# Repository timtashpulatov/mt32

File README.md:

# mt32
Ghetto synth

Prosthetic parts for lonely MT-32 board once salvaged at local flea market

##### Table of Contents
[Switch board](#sw_board)

[LCD](#lcd)

[POWER_SW](#power_sw)

<a name="sw_board"/>

## Switch board

- Switch board and LCD
")
")
</a>

Original switches marked SKELAF in the Service Manual:

Looks very similar to modern SKPLAFD010 from ALPS [(Datasheet)](PDF/ALPS-SKPLAFD010.pdf)

SKELAK was used in the Roland MKS-20 https://telcontar.net/KBK/Alps/elastic_contact

Check out SKEGAEA010 (with stem) [(Datasheet)](PDF/ALPS-SKEGAEA010.pdf)

Possible switches replacement:

- Omron B3M-6009
- Panasonic EVQ-PV205K [(Datasheet)](PDF/Panasonic-EVQ-PVA05K.pdf)
- E-Switch TL1140AF070Q

EVQ-PVA05K:

<a name="lcd"/>

## LCD module
DM2011 from Sanyo, with Epson SED1200 controller
</a>

<a name="power_sw"/>

## Power Switch
SPUN19F from ALPS
https://tech.alpsalpine.com/prod/e/html/switch/push/spun/spun19c400.html

## NOTES
DM2011 LCD module is clocked from SO7 port (pin 74 of IC35), via RC filter R62 (1K) and C83 (22p)

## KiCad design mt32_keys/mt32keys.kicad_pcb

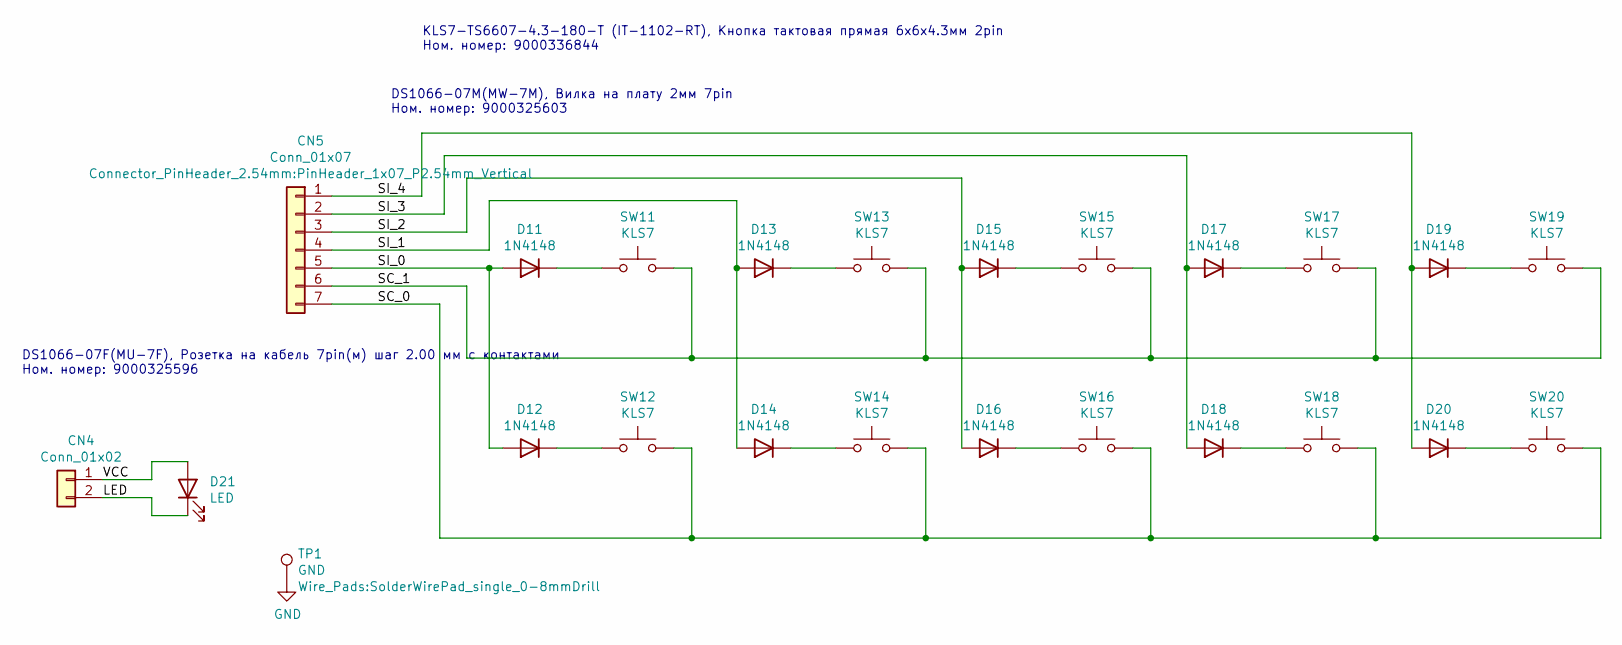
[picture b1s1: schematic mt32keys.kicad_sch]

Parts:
CN4: Conn_01x02; JST_NV_B02P-NV_2x5.00mm_Vertical
CN5: Conn_01x07; PinHeader_1x07_P2.54mm_Vertical
D11, D12, D13, D14, D15, D16, D17, D18, D19, D20: 1N4148; D_DO-35_SOD27_P10.16mm_Horizontal
D21: LED; LED_Rectangular_W3.0mm_H2.0mm
SW11, SW12, SW13, SW14, SW15, SW16, SW17, SW18, SW19, SW20: KLS7; KLS7-TS6607-4.3-180-T
TP1: GND; SolderWirePad_single_0-8mmDrill

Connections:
/LED: CN4.2, D21.1 (K)
/SC_0: CN5.7, SW12.2, SW14.2, SW16.2, SW18.2, SW20.2
/SC_1: CN5.6, SW11.2, SW13.2, SW15.2, SW17.2, SW19.2
/SI_0: CN5.5, D11.2 (A), D12.2 (A)
/SI_1: CN5.4, D13.2 (A), D14.2 (A)
/SI_2: CN5.3, D15.2 (A), D16.2 (A)
/SI_3: CN5.2, D17.2 (A), D18.2 (A)
/SI_4: CN5.1, D19.2 (A), D20.2 (A)
/VCC: CN4.1, D21.2 (A)
unnamed: D11.1 (K), SW11.1
unnamed: D12.1 (K), SW12.1
unnamed: D13.1 (K), SW13.1
unnamed: D14.1 (K), SW14.1
unnamed: D15.1 (K), SW15.1
unnamed: D16.1 (K), SW16.1
unnamed: D17.1 (K), SW17.1
unnamed: D18.1 (K), SW18.1
unnamed: D19.1 (K), SW19.1
unnamed: D20.1 (K), SW20.1

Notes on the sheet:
DS1066-07M(MW-7M), Вилка на плату 2мм 7pin Ном. номер: 9000325603
KLS7-TS6607-4.3-180-T (IT-1102-RT), Кнопка тактовая прямая 6х6х4.3мм 2pin Ном. номер: 9000336844
DS1066-07F(MU-7F), Розетка на кабель 7pin(м) шаг 2.00 мм с контактами Ном. номер: 9000325596

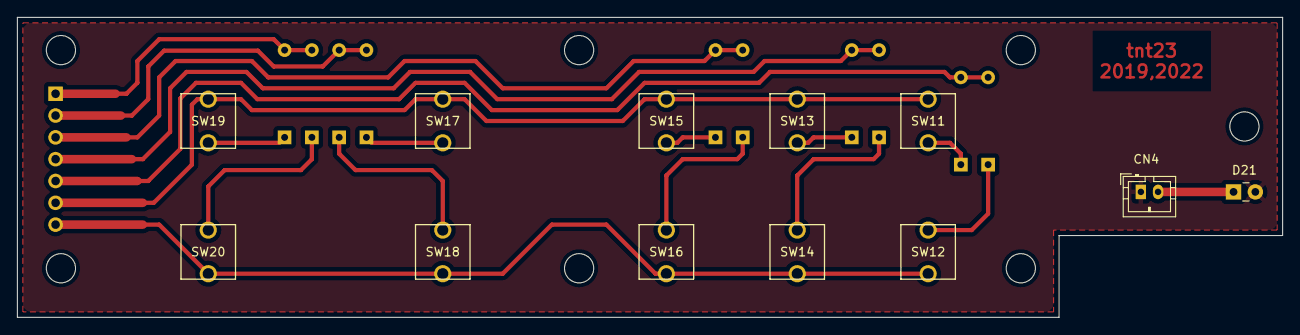
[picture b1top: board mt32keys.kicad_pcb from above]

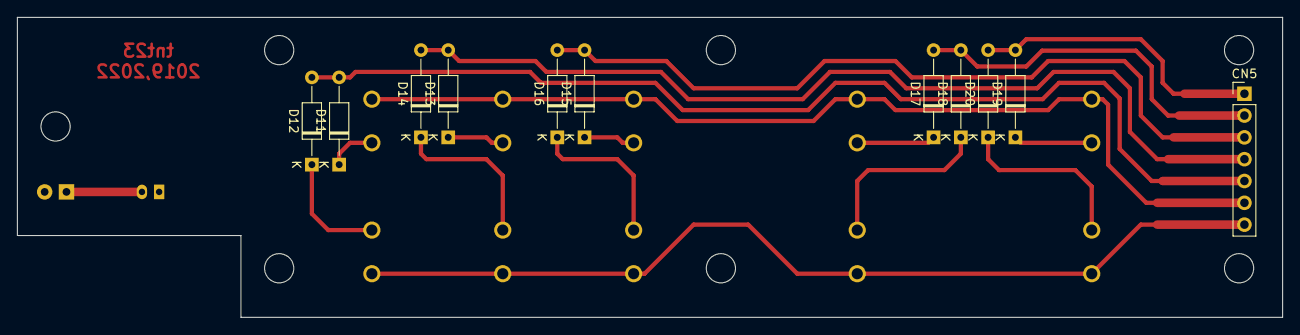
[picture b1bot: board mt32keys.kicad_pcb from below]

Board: 2 copper layers, 147.3 x 34.9 mm, 23 parts (11 on the bottom side), 19 nets.

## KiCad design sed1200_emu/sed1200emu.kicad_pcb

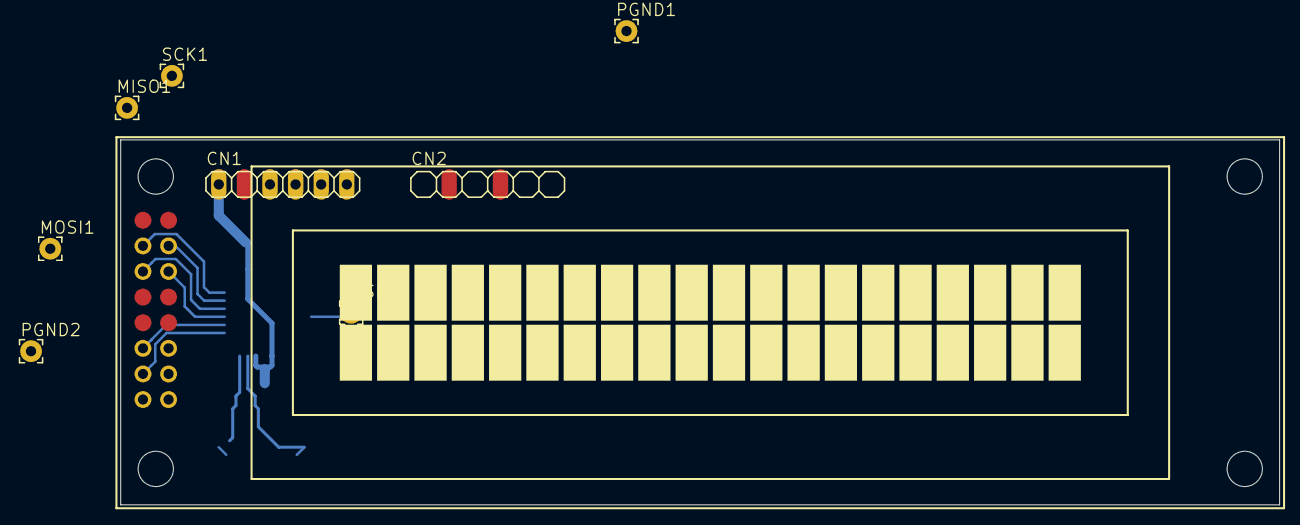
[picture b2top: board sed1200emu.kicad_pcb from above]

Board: 2 copper layers, 114.9 x 36.2 mm, 16 parts (0 on the bottom side), 21 nets.

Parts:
C1, C2: 0.1; C0805
C3, C4: 22p; C0805
CN1, CN2: PINHD-1X6; 1X06
DIS2: TUXGR_20X2
IC1: MEGA8-AI; TQFP32-08
MISO1: MISO; 2,15_1,0
MOSI1: MOSI; 2,15_1,0
PGND1, PGND2: 2,15_1,0
Q1: CRYSTALHC49S; Crystal_SMD_HC49-SD
R6: 330; M0805
RESET1: RESET; 2,15_1,0
SCK1: SCK; 2,15_1,0

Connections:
/D0: CN2.2-6, IC1.26
/D1: CN1.1-6, IC1.24
/D2: CN2.2-5, IC1.25
/D3: CN1.1-5, IC1.23
/E: CN1.1-4, IC1.1
/RS: CN2.2-3, IC1.27
/SO_6: CN1.1-3, IC1.32
GND: C1.2, C2.2, C3.1, C4.1, CN2.2-1, DIS2.1, DIS2.5, IC1.3, IC1.5, IC1.21, PGND1.1, PGND2.1
unnamed: C3.2, IC1.7, Q1.2
unnamed: C4.2, IC1.8, Q1.1
unnamed: DIS2.3, R6.2
unnamed: DIS2.4, IC1.10
unnamed: DIS2.6, IC1.11
unnamed: DIS2.11, IC1.12
unnamed: DIS2.12, IC1.13
unnamed: DIS2.13, IC1.14
unnamed: DIS2.14, IC1.15, MOSI1.1
unnamed: IC1.16, MISO1.1
unnamed: IC1.17, SCK1.1
unnamed: IC1.29, RESET1.1
VCC: C1.1, C2.1, CN1.1-1, DIS2.2, IC1.4, IC1.6, IC1.18, R6.1

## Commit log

2019-12-09 Initial (well, not quite) commit
2019-12-09 Plotting
2019-12-10 Create placeholder
2019-12-11 Switch 3d model added
2019-12-11 PCB: Update 3d models for switches; add render
2019-12-11 Comments on dimensions added
2019-12-12 Port sed1200emu
2019-12-13 Update PCB
2019-12-13 More SMD pads
2019-12-14 Foto of original switch board
2022-01-04 Last updates
2022-01-04 Updated for real size
2022-01-04 Add more photos of SW board and LCD assy
2022-01-04 Update for KiCad 6
2022-01-04 Update 3d models and silk
2022-01-04 Add SKEGAEA010 datasheet
2022-01-10 More SKEL info
